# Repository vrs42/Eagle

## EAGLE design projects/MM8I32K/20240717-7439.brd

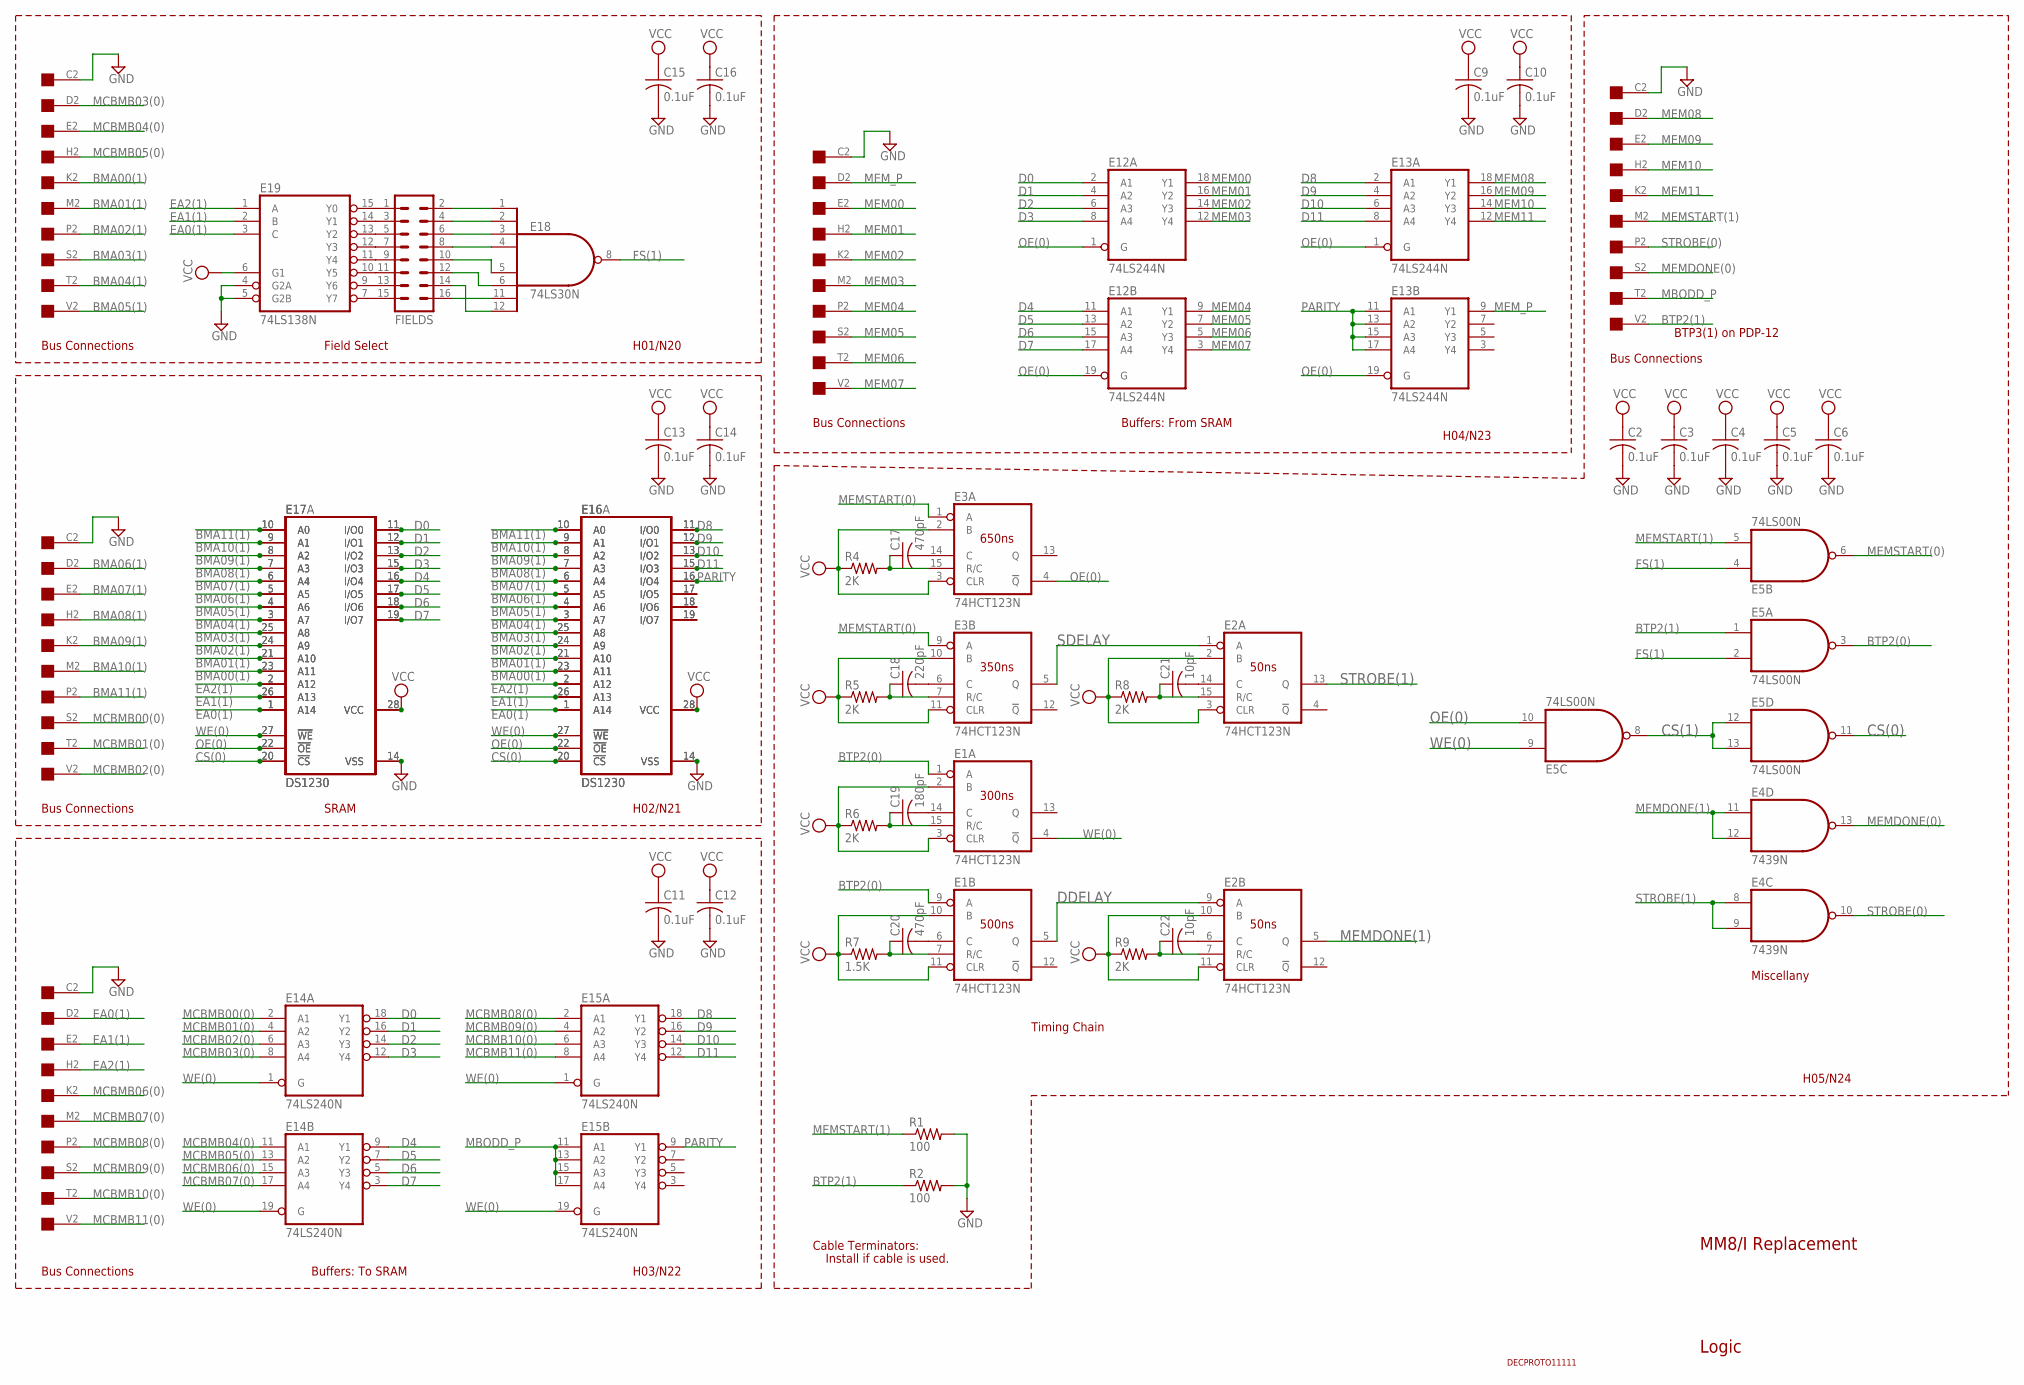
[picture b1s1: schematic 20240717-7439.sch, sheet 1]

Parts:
C2, C3, C4, C5, C6, C9, C10, C11, C12, C13, C14, C15, C16: 0.1uF; C050-025X075
C17, C20: 470pF; C050-025X075
C18: 220pF; C050-025X075
C19: 180pF; C050-025X075
C21, C22: 10pF; C050-025X075
E1, E2, E3: 74HCT123N; DIL16
E4: 7439N; DIL14
E5: 74LS00N; DIL14
E12, E13: 74LS244N; DIL20
E14, E15: 74LS240N; DIL20
E16, E17: DS1230; DIL28-6
E16A, E17A: DS1230; DIL28-3
E18: 74LS30N; DIL14
E19: 74LS138N; DIL16
FIELDS: MA08-2
H01, H02, H03, H04, H05: EDGE-CON1
R1, R2: 100; 0207/10
R4, R5, R6, R8, R9: 2K; 0207/10
R7: 1.5K; 0207/10
U$6: DECPROTO11111

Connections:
BMA00(1): E16.23 (A11), E16A.23 (A11), E17.23 (A11), E17A.23 (A11), H01.K2; also elsewhere on the board
BMA01(1): E16.21 (A10), E16A.21 (A10), E17.21 (A10), E17A.21 (A10), H01.M2; also elsewhere on the board
BMA02(1): E16.24 (A9), E16A.24 (A9), E17.24 (A9), E17A.24 (A9), H01.P2; also elsewhere on the board
BMA03(1): E16.25 (A8), E16A.25 (A8), E17.25 (A8), E17A.25 (A8), H01.S2; also elsewhere on the board
BMA04(1): E16.3 (A7), E16A.3 (A7), E17.3 (A7), E17A.3 (A7), H01.T2; also elsewhere on the board
BMA05(1): E16.4 (A6), E16A.4 (A6), E17.4 (A6), E17A.4 (A6), H01.V2; also elsewhere on the board
BMA06(1): E16.5 (A5), E16A.5 (A5), E17.5 (A5), E17A.5 (A5), H02.D2; also elsewhere on the board
BMA07(1): E16.6 (A4), E16A.6 (A4), E17.6 (A4), E17A.6 (A4), H02.E2; also elsewhere on the board
BMA08(1): E16.7 (A3), E16A.7 (A3), E17.7 (A3), E17A.7 (A3), H02.H2; also elsewhere on the board
BMA09(1): E16.8 (A2), E16A.8 (A2), E17.8 (A2), E17A.8 (A2), H02.K2; also elsewhere on the board
BMA10(1): E16.9 (A1), E16A.9 (A1), E17.9 (A1), E17A.9 (A1), H02.M2; also elsewhere on the board
BMA11(1): E16.10 (A0), E16A.10 (A0), E17.10 (A0), E17A.10 (A0), H02.P2; also elsewhere on the board
BTP2(0): E1.1 (A), E1.9 (A), E5.3 (O)
BTP2(1): E5.1 (I0), H05.V2, R2.1
CS(0): E5.11 (O), E16.20 (!CS), E16A.20 (!CS), E17.20 (!CS), E17A.20 (!CS); also elsewhere on the board
CS(1): E5.8 (O), E5.12 (I0), E5.13 (I1)
D0: E12.2 (A1), E14.18 (Y1), E17.11 (I/O0), E17A.11 (I/O0); also elsewhere on the board
D1: E12.4 (A2), E14.16 (Y2), E17.12 (I/O1), E17A.12 (I/O1); also elsewhere on the board
D2: E12.6 (A3), E14.14 (Y3), E17.13 (I/O2), E17A.13 (I/O2); also elsewhere on the board
D3: E12.8 (A4), E14.12 (Y4), E17.15 (I/O3), E17A.15 (I/O3); also elsewhere on the board
D4: E12.11 (A1), E14.9 (Y1), E17.16 (I/O4), E17A.16 (I/O4); also elsewhere on the board
D5: E12.13 (A2), E14.7 (Y2), E17.17 (I/O5), E17A.17 (I/O5); also elsewhere on the board
D6: E12.15 (A3), E14.5 (Y3), E17.18 (I/O6), E17A.18 (I/O6); also elsewhere on the board
D7: E12.17 (A4), E14.3 (Y4), E17.19 (I/O7), E17A.19 (I/O7); also elsewhere on the board
D8: E13.2 (A1), E15.18 (Y1), E16.11 (I/O0), E16A.11 (I/O0); also elsewhere on the board
D9: E13.4 (A2), E15.16 (Y2), E16.12 (I/O1), E16A.12 (I/O1); also elsewhere on the board
D10: E13.6 (A3), E15.14 (Y3), E16.13 (I/O2), E16A.13 (I/O2); also elsewhere on the board
D11: E13.8 (A4), E15.12 (Y4), E16.15 (I/O3), E16A.15 (I/O3); also elsewhere on the board
DDELAY: E1.5 (Q), E2.9 (A)
EA0(1): E16.1 (A14), E16A.1 (A14), E17.1 (A14), E17A.1 (A14), E19.3 (C), H03.D2; also elsewhere on the board
EA1(1): E16.26 (A13), E16A.26 (A13), E17.26 (A13), E17A.26 (A13), E19.2 (B), H03.E2; also elsewhere on the board
EA2(1): E16.2 (A12), E16A.2 (A12), E17.2 (A12), E17A.2 (A12), E19.1 (A), H03.H2; also elsewhere on the board
FS(1): E5.2 (I1), E5.4 (I0), E18.8 (O); also elsewhere on the board
GND: C2.2, C3.2, C4.2, C5.2, C6.2, C9.2, C10.2, C11.2, C12.2, C13.2, C14.2, C15.2, C16.2, E1.8 (GND), E2.8 (GND), E3.8 (GND), E4.7 (GND), E5.7 (GND), E12.10 (GND), E13.10 (GND), E14.10 (GND), E15.10 (GND), E16.14 (VSS), E16A.14 (VSS), E17.14 (VSS), E17A.14 (VSS), E18.7 (GND), E19.4 (G2A), E19.5 (G2B), E19.8 (GND), H01.C2, H02.C2, H03.C2, H04.C2, H05.C2, R1.2, R2.2; also elsewhere on the board
MBODD_P: E15.11 (A1), E15.13 (A2), E15.15 (A3), E15.17 (A4), H05.T2; also elsewhere on the board
MCBMB00(0): E14.2 (A1), H02.S2; also elsewhere on the board
MCBMB01(0): E14.4 (A2), H02.T2; also elsewhere on the board
MCBMB02(0): E14.6 (A3), H02.V2; also elsewhere on the board
MCBMB03(0): E14.8 (A4), H01.D2; also elsewhere on the board
MCBMB04(0): E14.11 (A1), H01.E2; also elsewhere on the board
MCBMB05(0): E14.13 (A2), H01.H2; also elsewhere on the board
MCBMB06(0): E14.15 (A3), H03.K2
MCBMB07(0): E14.17 (A4), H03.M2
MCBMB08(0): E15.2 (A1), H03.P2
MCBMB09(0): E15.4 (A2), H03.S2
MCBMB10(0): E15.6 (A3), H03.T2
MCBMB11(0): E15.8 (A4), H03.V2
MEM00: E12.18 (Y1), H04.E2
MEM01: E12.16 (Y2), H04.H2
MEM02: E12.14 (Y3), H04.K2
MEM03: E12.12 (Y4), H04.M2
MEM04: E12.9 (Y1), H04.P2
MEM05: E12.7 (Y2), H04.S2
MEM06: E12.5 (Y3), H04.T2
MEM07: E12.3 (Y4), H04.V2
MEM08: E13.18 (Y1), H05.D2; also elsewhere on the board
MEM09: E13.16 (Y2), H05.E2; also elsewhere on the board
MEM10: E13.14 (Y3), H05.H2; also elsewhere on the board
MEM11: E13.12 (Y4), H05.K2; also elsewhere on the board
MEMDONE(0): E4.13 (O), H05.S2
MEMDONE(1): E2.5 (Q), E4.11 (I0), E4.12 (I1)
MEMSTART(0): E3.1 (A), E3.9 (A), E5.6 (O)
MEMSTART(1): E5.5 (I1), H05.M2, R1.1
MEM_P: E13.9 (Y1), H04.D2
unnamed: E16.17 (I/O5), E16A.17 (I/O5)
unnamed: E16.18 (I/O6), E16A.18 (I/O6)
unnamed: E16.19 (I/O7), E16A.19 (I/O7)
unnamed: C17.1, E3.15 (R/C), R4.2
unnamed: C17.2, E3.14 (C)
unnamed: C18.1, E3.7 (R/C), R5.2
unnamed: C18.2, E3.6 (C)
unnamed: C19.1, E1.15 (R/C), R6.2
unnamed: C19.2, E1.14 (C)
unnamed: C20.1, E1.7 (R/C), R7.2
unnamed: C20.2, E1.6 (C)
unnamed: C21.1, E2.15 (R/C), R8.2
unnamed: C21.2, E2.14 (C)
unnamed: C22.1, E2.7 (R/C), R9.2
unnamed: C22.2, E2.6 (C)
unnamed: E19.15 (Y0), FIELDS.1
unnamed: E19.14 (Y1), FIELDS.3
unnamed: E19.13 (Y2), FIELDS.5
unnamed: E19.12 (Y3), FIELDS.7
unnamed: E19.11 (Y4), FIELDS.9
unnamed: E19.10 (Y5), FIELDS.11
unnamed: E19.9 (Y6), FIELDS.13
unnamed: E19.7 (Y7), FIELDS.15
unnamed: E18.4 (I3), FIELDS.8
unnamed: E18.3 (I2), FIELDS.6
unnamed: E18.2 (I1), FIELDS.4
unnamed: E18.1 (I0), FIELDS.2
unnamed: E18.5 (I4), FIELDS.10
unnamed: E18.6 (I5), FIELDS.12
unnamed: E18.12 (I7), FIELDS.14
unnamed: E18.11 (I6), FIELDS.16
OE(0): E3.4 (!Q), E5.10 (I1), E12.1 (G), E12.19 (G), E13.1 (G), E13.19 (G), E16.22 (!OE), E16A.22 (!OE), E17.22 (!OE), E17A.22 (!OE); also elsewhere on the board
PARITY: E13.11 (A1), E13.13 (A2), E13.15 (A3), E13.17 (A4), E15.9 (Y1), E16.16 (I/O4), E16A.16 (I/O4); also elsewhere on the board
SDELAY: E2.1 (A), E3.5 (Q)
STROBE(0): E4.10 (O), H05.P2
STROBE(1): E2.13 (Q), E4.8 (I0), E4.9 (I1)
VCC: C2.1, C3.1, C4.1, C5.1, C6.1, C9.1, C10.1, C11.1, C12.1, C13.1, C14.1, C15.1, C16.1, E1.2 (B), E1.3 (CLR), E1.10 (B), E1.11 (CLR), E1.16 (VCC), E2.2 (B), E2.3 (CLR), E2.10 (B), E2.11 (CLR), E2.16 (VCC), E3.2 (B), E3.3 (CLR), E3.10 (B), E3.11 (CLR), E3.16 (VCC), E4.14 (VCC), E5.14 (VCC), E12.20 (VCC), E13.20 (VCC), E14.20 (VCC), E15.20 (VCC), E16.28 (VCC), E16A.28 (VCC), E17.28 (VCC), E17A.28 (VCC), E18.14 (VCC), E19.6 (G1), E19.16 (VCC), R4.1, R5.1, R6.1, R7.1, R8.1, R9.1; also elsewhere on the board
WE(0): E1.4 (!Q), E5.9 (I0), E14.1 (G), E14.19 (G), E15.1 (G), E15.19 (G), E16.27 (!WE), E16A.27 (!WE), E17.27 (!WE), E17A.27 (!WE); also elsewhere on the board

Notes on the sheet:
H01/N20
H02/N21
H03/N22
H04/N23
Field Select
SRAM
MM8/I Replacement
Buffers: To SRAM
Buffers: From SRAM
Timing Chain
BTP3(1) on PDP-12
Miscellany
H05/N24
Logic
Bus Connections
Cable Terminators:
Install if cable is used.
650ns
350ns
50ns
300ns
500ns

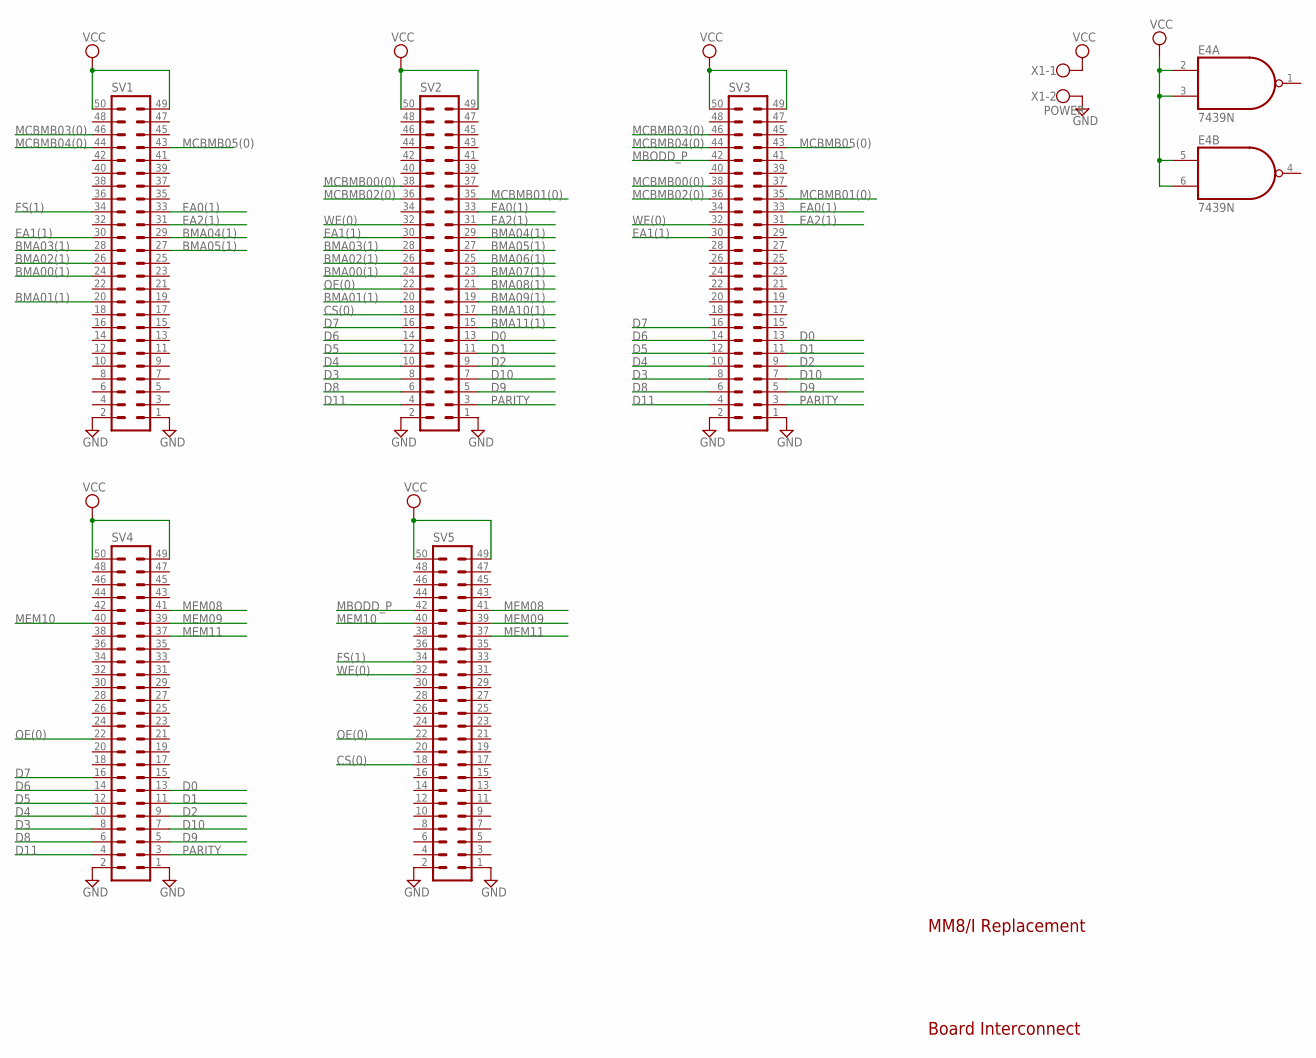
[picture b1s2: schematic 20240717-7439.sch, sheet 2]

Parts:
E4: 7439N; DIL14
SV1, SV2, SV3, SV4, SV5: ML50L
X1: POWER; W237-102

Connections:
BMA00(1): SV1.24, SV2.24; also elsewhere on the board
BMA01(1): SV1.20, SV2.20; also elsewhere on the board
BMA02(1): SV1.26, SV2.26; also elsewhere on the board
BMA03(1): SV1.28, SV2.28; also elsewhere on the board
BMA04(1): SV1.29, SV2.29; also elsewhere on the board
BMA05(1): SV1.27, SV2.27; also elsewhere on the board
BMA06(1): SV2.25; also elsewhere on the board
BMA07(1): SV2.23; also elsewhere on the board
BMA08(1): SV2.21; also elsewhere on the board
BMA09(1): SV2.19; also elsewhere on the board
BMA10(1): SV2.17; also elsewhere on the board
BMA11(1): SV2.15; also elsewhere on the board
CS(0): SV2.18, SV5.18; also elsewhere on the board
D0: SV2.13, SV3.13, SV4.13; also elsewhere on the board
D1: SV2.11, SV3.11, SV4.11; also elsewhere on the board
D2: SV2.9, SV3.9, SV4.9; also elsewhere on the board
D3: SV2.8, SV3.8, SV4.8; also elsewhere on the board
D4: SV2.10, SV3.10, SV4.10; also elsewhere on the board
D5: SV2.12, SV3.12, SV4.12; also elsewhere on the board
D6: SV2.14, SV3.14, SV4.14; also elsewhere on the board
D7: SV2.16, SV3.16, SV4.16; also elsewhere on the board
D8: SV2.6, SV3.6, SV4.6; also elsewhere on the board
D9: SV2.5, SV3.5, SV4.5; also elsewhere on the board
D10: SV2.7, SV3.7, SV4.7; also elsewhere on the board
D11: SV2.4, SV3.4, SV4.4; also elsewhere on the board
EA0(1): SV1.33, SV2.33, SV3.33; also elsewhere on the board
EA1(1): SV1.30, SV2.30, SV3.30; also elsewhere on the board
EA2(1): SV1.31, SV2.31, SV3.31; also elsewhere on the board
FS(1): SV1.34, SV5.34; also elsewhere on the board
GND: E4.7 (GND), SV1.1, SV1.2, SV2.1, SV2.2, SV3.1, SV3.2, SV4.1, SV4.2, SV5.1, SV5.2, X1.2; also elsewhere on the board
MBODD_P: SV3.42, SV5.42; also elsewhere on the board
MCBMB00(0): SV2.38, SV3.38; also elsewhere on the board
MCBMB01(0): SV2.35, SV3.35; also elsewhere on the board
MCBMB02(0): SV2.36, SV3.36; also elsewhere on the board
MCBMB03(0): SV1.46, SV3.46; also elsewhere on the board
MCBMB04(0): SV1.44, SV3.44; also elsewhere on the board
MCBMB05(0): SV1.43, SV3.43; also elsewhere on the board
MEM08: SV4.41, SV5.41; also elsewhere on the board
MEM09: SV4.39, SV5.39; also elsewhere on the board
MEM10: SV4.40, SV5.40; also elsewhere on the board
MEM11: SV4.37, SV5.37; also elsewhere on the board
OE(0): SV2.22, SV4.22, SV5.22; also elsewhere on the board
PARITY: SV2.3, SV3.3, SV4.3; also elsewhere on the board
VCC: E4.2 (I0), E4.3 (I1), E4.5 (I0), E4.6 (I1), E4.14 (VCC), SV1.49, SV1.50, SV2.49, SV2.50, SV3.49, SV3.50, SV4.49, SV4.50, SV5.49, SV5.50, X1.1; also elsewhere on the board
WE(0): SV2.32, SV3.32, SV5.32; also elsewhere on the board

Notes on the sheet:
Board Interconnect
MM8/I Replacement

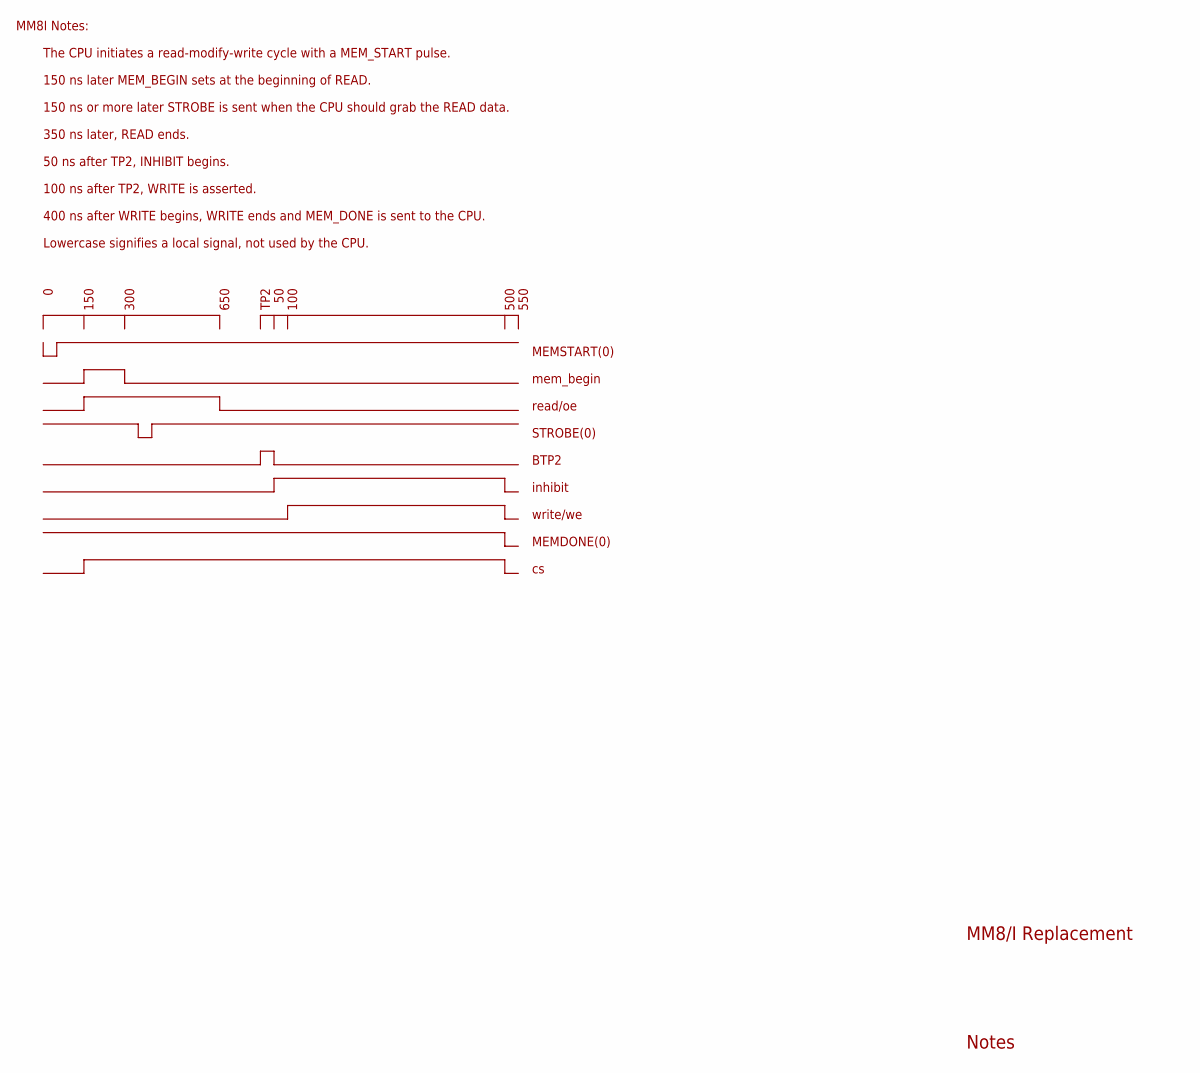
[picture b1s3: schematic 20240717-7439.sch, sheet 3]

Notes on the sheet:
Notes
The CPU initiates a read-modify-write cycle with a MEM_START pulse.
150 ns later MEM_BEGIN sets at the beginning of READ.
150 ns or more later STROBE is sent when the CPU should grab the READ data.
50 ns after TP2, INHIBIT begins.
100 ns after TP2, WRITE is asserted.
400 ns after WRITE begins, WRITE ends and MEM_DONE is sent to the CPU.
350 ns later, READ ends.
150
300
650
TP2
100
500
MEMSTART(0)
mem_begin
read/oe
STROBE(0)
BTP2
inhibit
write/we
MEMDONE(0)
Lowercase signifies a local signal, not used by the CPU.
550
MM8I Notes:
MM8/I Replacement

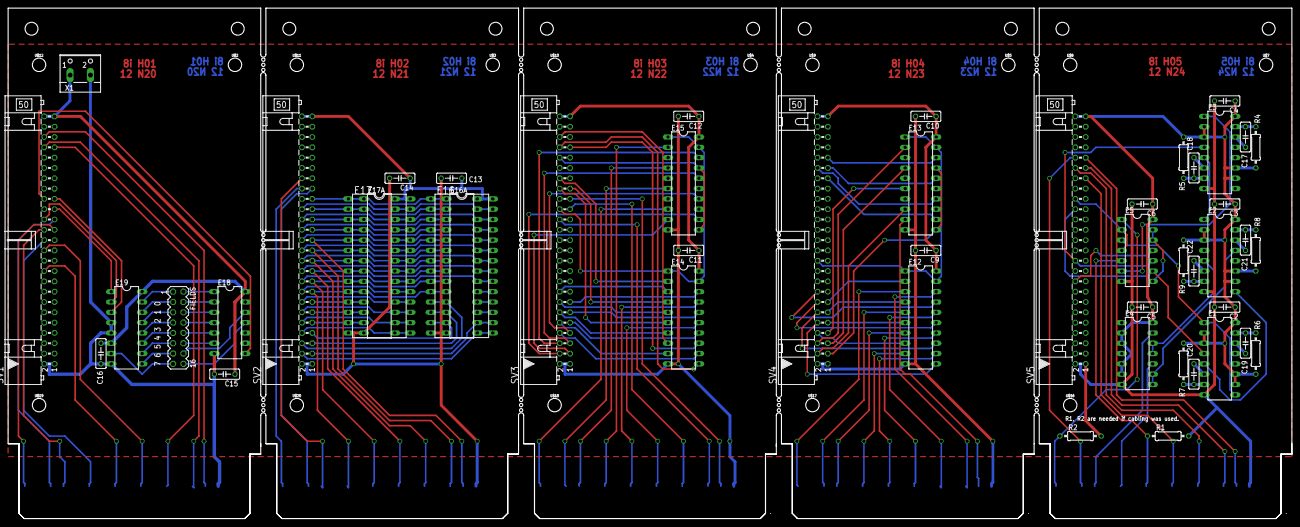
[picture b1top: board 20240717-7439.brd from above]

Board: 2 copper layers, 316.2 x 125.7 mm, 70 parts (0 on the bottom side), 102 nets.

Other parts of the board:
U$2, U$3, U$4, U$5, U$7, U$8, U$9, U$10, U$11, U$12, U$16, U$17, U$18, U$19, U$20: STAND-OFF

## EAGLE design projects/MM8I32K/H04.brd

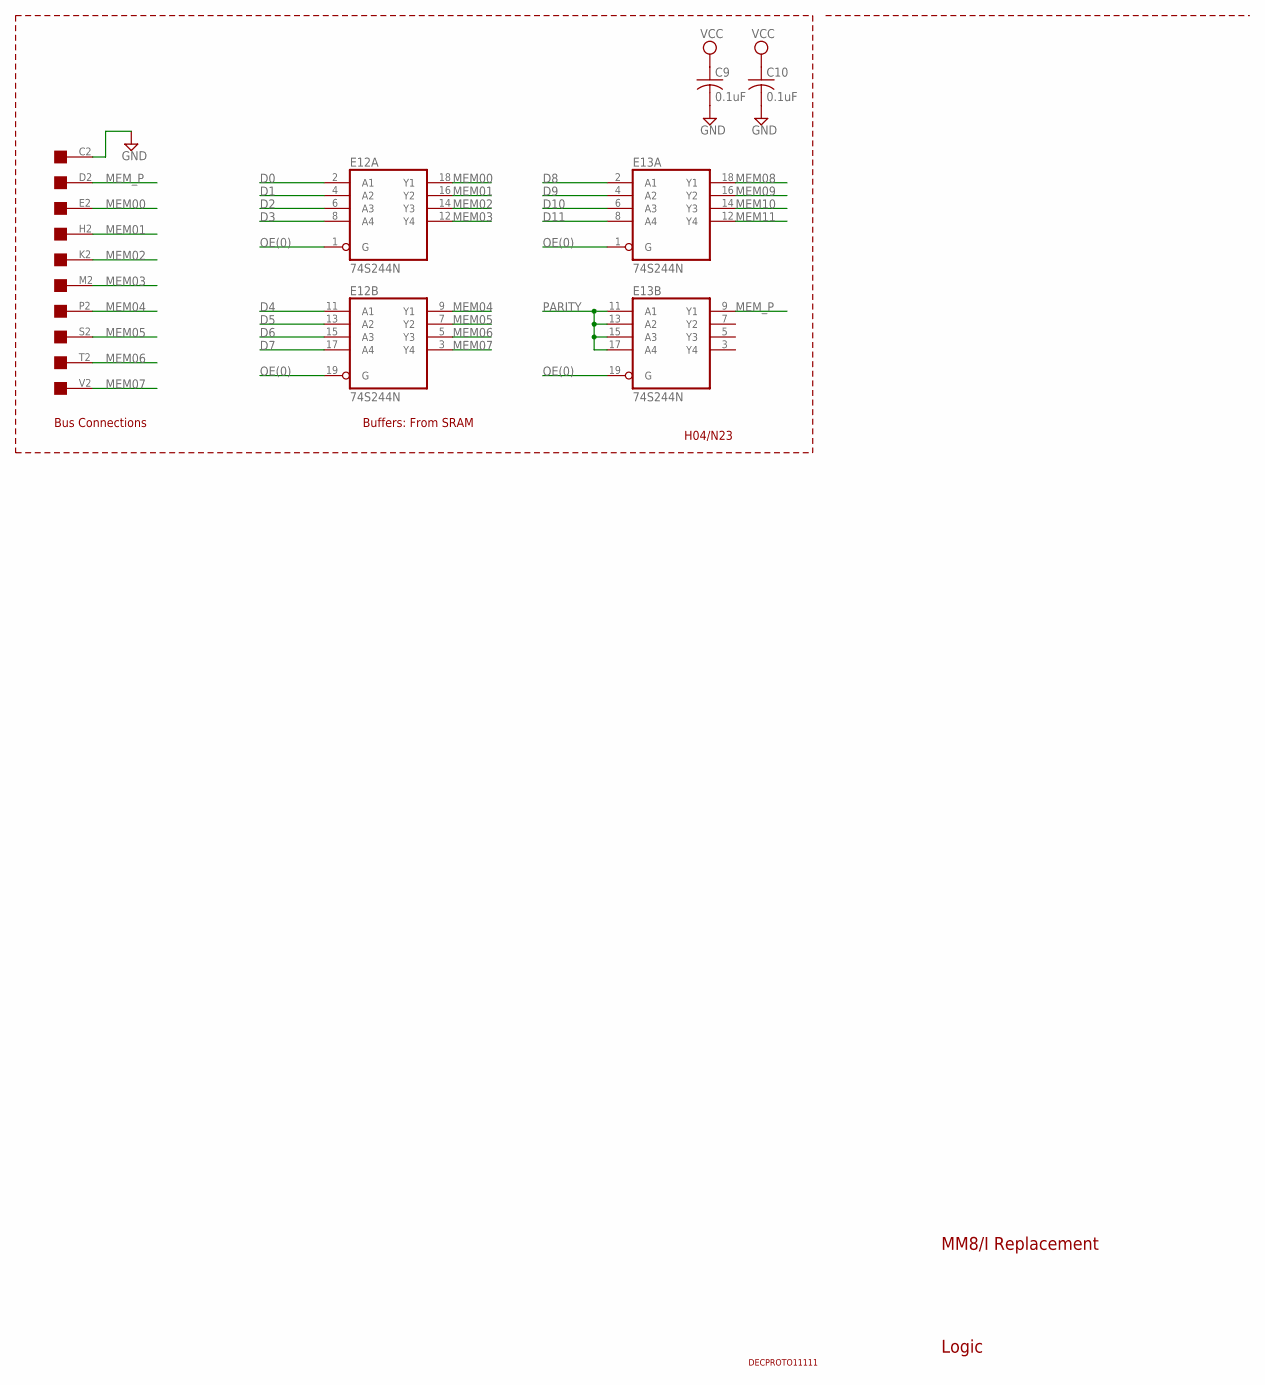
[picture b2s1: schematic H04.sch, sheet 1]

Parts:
C9, C10: 0.1uF; C050-025X075
E12, E13: 74S244N; DIL20
H04: EDGE-CON1
U$6: DECPROTO11111

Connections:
D0: E12.2 (A1); also elsewhere on the board
D1: E12.4 (A2); also elsewhere on the board
D2: E12.6 (A3); also elsewhere on the board
D3: E12.8 (A4); also elsewhere on the board
D4: E12.11 (A1); also elsewhere on the board
D5: E12.13 (A2); also elsewhere on the board
D6: E12.15 (A3); also elsewhere on the board
D7: E12.17 (A4); also elsewhere on the board
D8: E13.2 (A1); also elsewhere on the board
D9: E13.4 (A2); also elsewhere on the board
D10: E13.6 (A3); also elsewhere on the board
D11: E13.8 (A4); also elsewhere on the board
GND: C9.2, C10.2, E12.10 (GND), E13.10 (GND), H04.C2; also elsewhere on the board
MEM00: E12.18 (Y1), H04.E2
MEM01: E12.16 (Y2), H04.H2
MEM02: E12.14 (Y3), H04.K2
MEM03: E12.12 (Y4), H04.M2
MEM04: E12.9 (Y1), H04.P2
MEM05: E12.7 (Y2), H04.S2
MEM06: E12.5 (Y3), H04.T2
MEM07: E12.3 (Y4), H04.V2
MEM08: E13.18 (Y1); also elsewhere on the board
MEM09: E13.16 (Y2); also elsewhere on the board
MEM10: E13.14 (Y3); also elsewhere on the board
MEM11: E13.12 (Y4); also elsewhere on the board
MEM_P: E13.9 (Y1), H04.D2
OE(0): E12.1 (G), E12.19 (G), E13.1 (G), E13.19 (G); also elsewhere on the board
PARITY: E13.11 (A1), E13.13 (A2), E13.15 (A3), E13.17 (A4); also elsewhere on the board
VCC: C9.1, C10.1, E12.20 (VCC), E13.20 (VCC); also elsewhere on the board

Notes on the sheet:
H04/N23
MM8/I Replacement
Buffers: From SRAM
Logic
Bus Connections

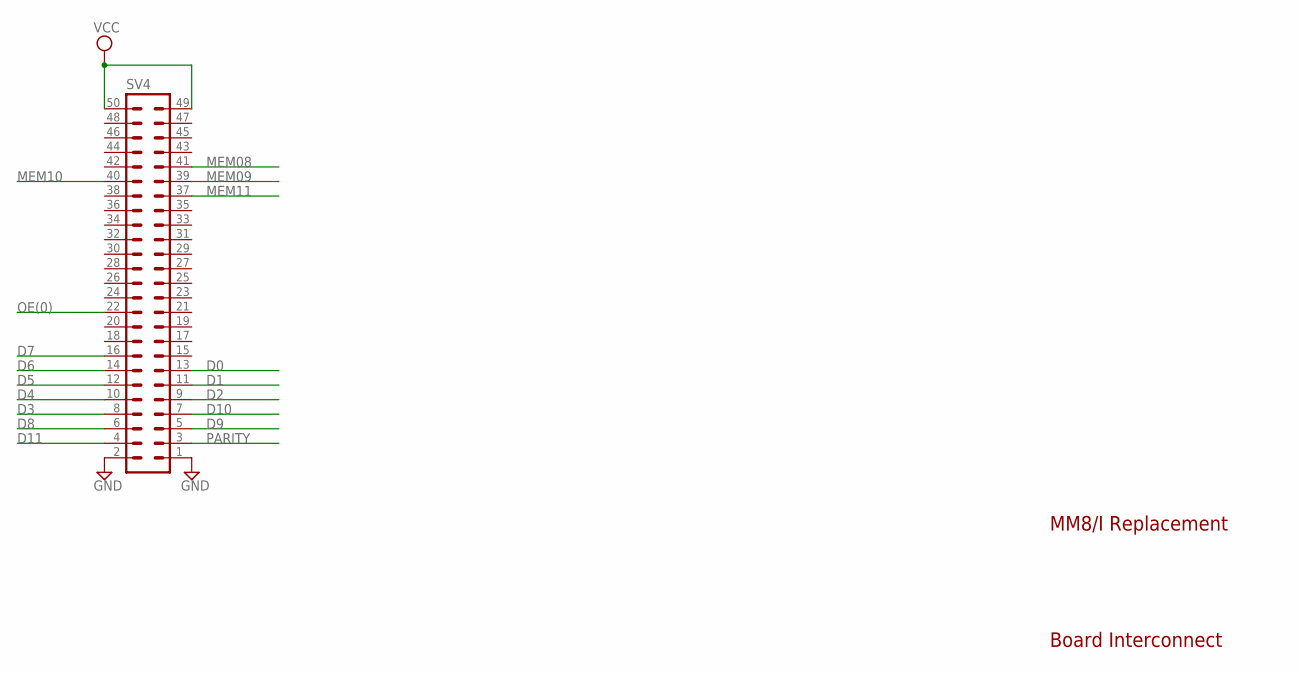
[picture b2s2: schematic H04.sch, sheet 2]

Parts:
SV4: ML50L

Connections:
D0: SV4.13; also elsewhere on the board
D1: SV4.11; also elsewhere on the board
D2: SV4.9; also elsewhere on the board
D3: SV4.8; also elsewhere on the board
D4: SV4.10; also elsewhere on the board
D5: SV4.12; also elsewhere on the board
D6: SV4.14; also elsewhere on the board
D7: SV4.16; also elsewhere on the board
D8: SV4.6; also elsewhere on the board
D9: SV4.5; also elsewhere on the board
D10: SV4.7; also elsewhere on the board
D11: SV4.4; also elsewhere on the board
GND: SV4.1, SV4.2; also elsewhere on the board
MEM08: SV4.41; also elsewhere on the board
MEM09: SV4.39; also elsewhere on the board
MEM10: SV4.40; also elsewhere on the board
MEM11: SV4.37; also elsewhere on the board
OE(0): SV4.22; also elsewhere on the board
PARITY: SV4.3; also elsewhere on the board
VCC: SV4.49, SV4.50; also elsewhere on the board

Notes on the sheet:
Board Interconnect
MM8/I Replacement

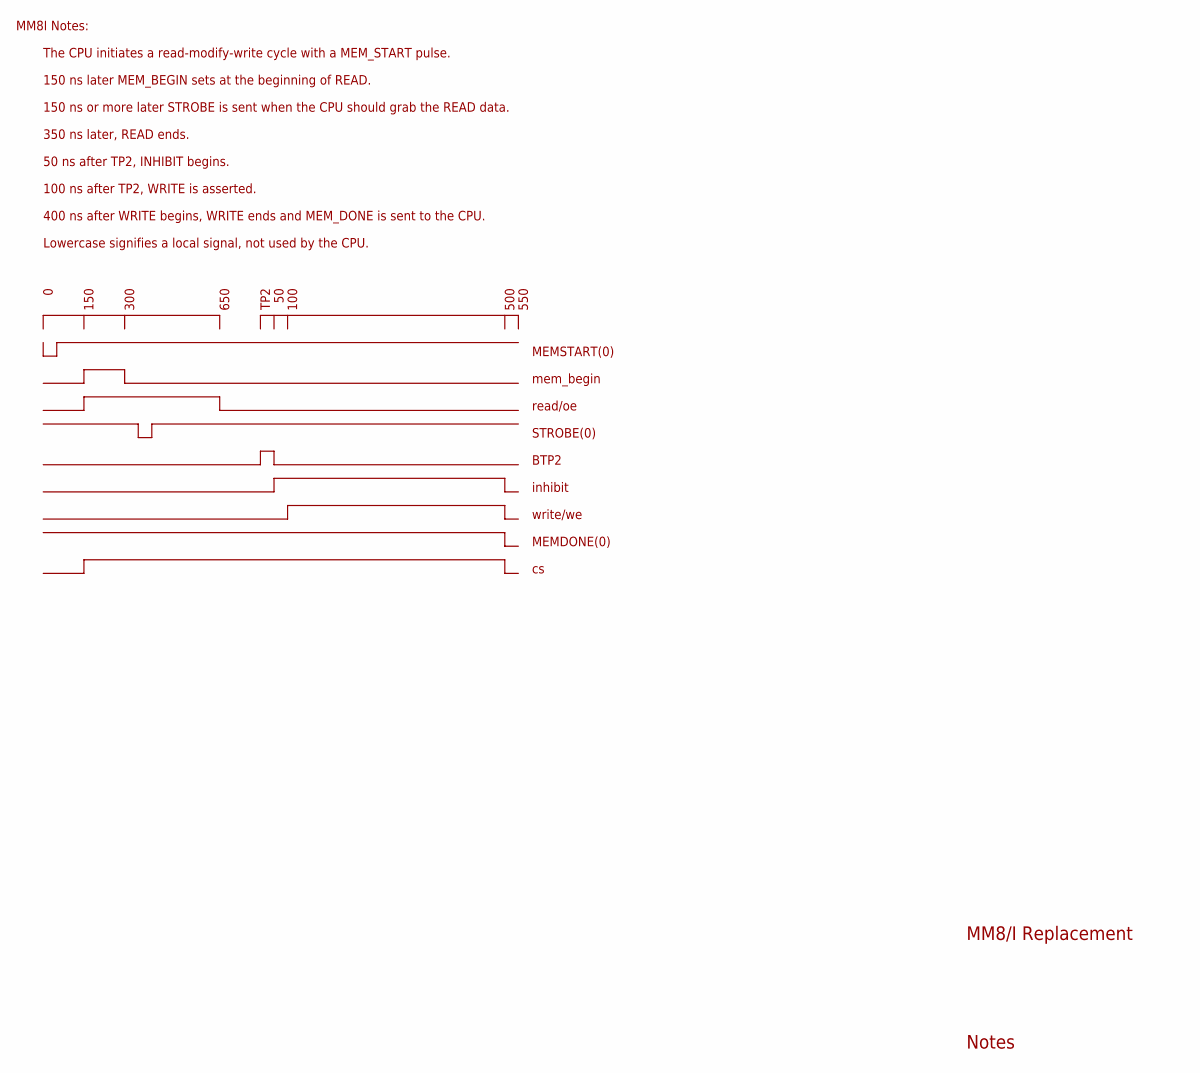
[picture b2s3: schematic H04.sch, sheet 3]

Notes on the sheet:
Notes
The CPU initiates a read-modify-write cycle with a MEM_START pulse.
150 ns later MEM_BEGIN sets at the beginning of READ.
150 ns or more later STROBE is sent when the CPU should grab the READ data.
50 ns after TP2, INHIBIT begins.
100 ns after TP2, WRITE is asserted.
400 ns after WRITE begins, WRITE ends and MEM_DONE is sent to the CPU.
350 ns later, READ ends.
150
300
650
TP2
100
500
MEMSTART(0)
mem_begin
read/oe
STROBE(0)
BTP2
inhibit
write/we
MEMDONE(0)
Lowercase signifies a local signal, not used by the CPU.
550
MM8I Notes:
MM8/I Replacement

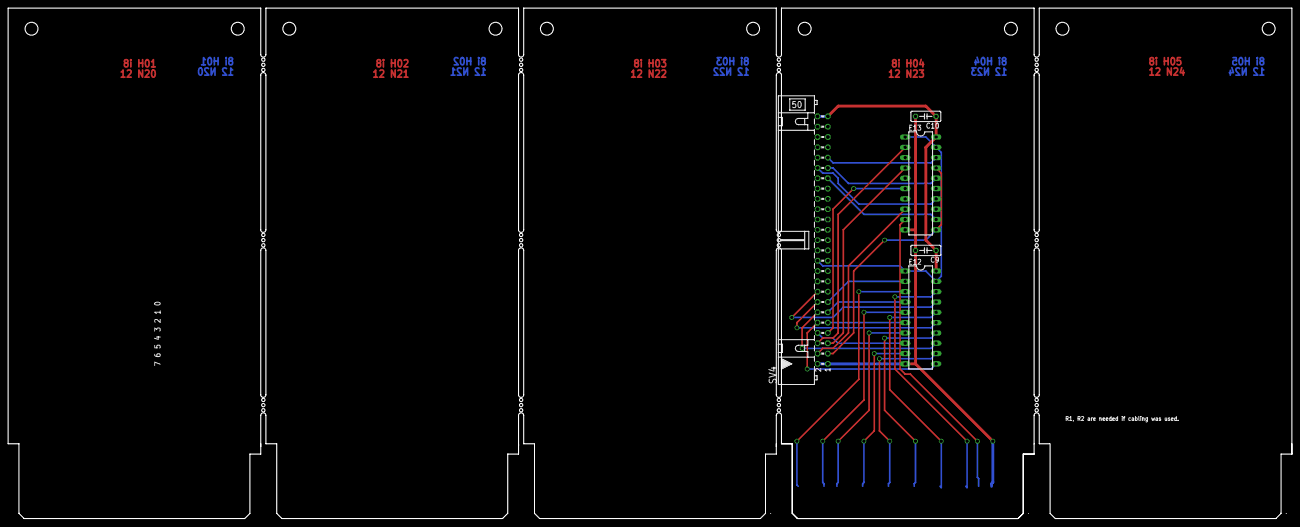
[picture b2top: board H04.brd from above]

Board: 2 copper layers, 316.2 x 125.7 mm, 7 parts (0 on the bottom side), 29 nets.

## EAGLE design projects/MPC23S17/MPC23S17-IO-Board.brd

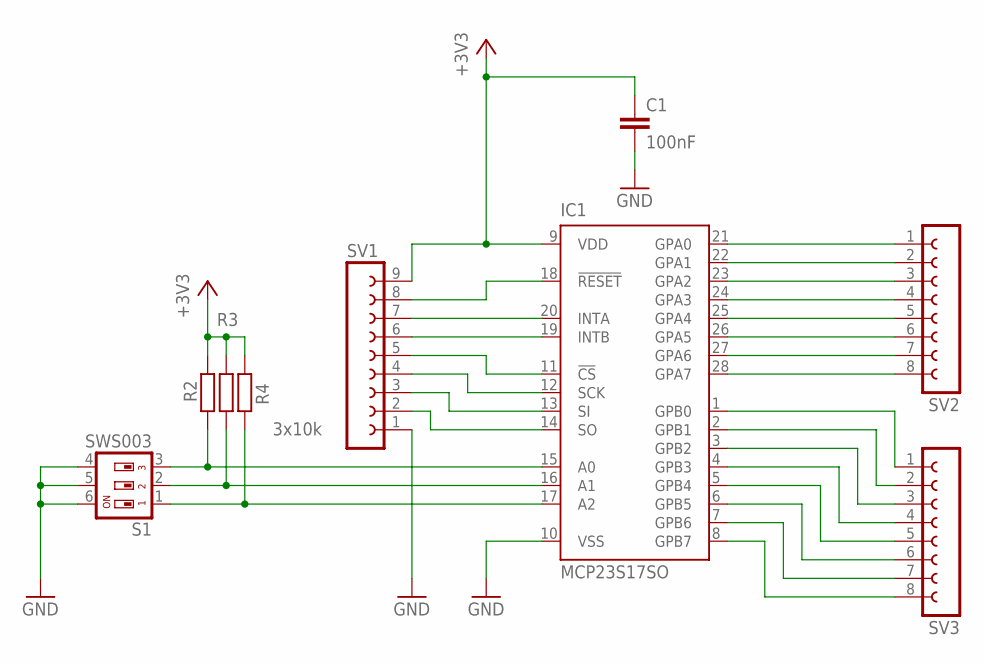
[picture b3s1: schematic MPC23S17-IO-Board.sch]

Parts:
C1: 100nF; C1206
IC1: MCP23S17SO; SO28W
R2, R3: 10k; M1206
R4: 3x10k; M1206
S1: SWS003; SMS-003
SV1: FE09-1; FE09
SV2, SV3: FE08-1; FE08

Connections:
+3V3: C1.1, IC1.9 (VDD), R2.1, R3.1, R4.1, SV1.9
GND: C1.2, IC1.10 (VSS), S1.4, S1.5, S1.6, SV1.1
unnamed: IC1.21 (GPA0), SV2.1
unnamed: IC1.22 (GPA1), SV2.2
unnamed: IC1.23 (GPA2), SV2.3
unnamed: IC1.24 (GPA3), SV2.4
unnamed: IC1.25 (GPA4), SV2.5
unnamed: IC1.26 (GPA5), SV2.6
unnamed: IC1.27 (GPA6), SV2.7
unnamed: IC1.28 (GPA7), SV2.8
unnamed: IC1.1 (GPB0), SV3.1
unnamed: IC1.2 (GPB1), SV3.2
unnamed: IC1.3 (GPB2), SV3.3
unnamed: IC1.4 (GPB3), SV3.4
unnamed: IC1.5 (GPB4), SV3.5
unnamed: IC1.15 (A0), R2.2, S1.3
unnamed: IC1.16 (A1), R3.2, S1.2
unnamed: IC1.17 (A2), R4.2, S1.1
unnamed: IC1.6 (GPB5), SV3.6
unnamed: IC1.7 (GPB6), SV3.7
unnamed: IC1.19 (INTB), SV1.6
unnamed: IC1.14 (SO), SV1.2
unnamed: IC1.13 (SI), SV1.3
unnamed: IC1.12 (SCK), SV1.4
unnamed: IC1.11 (!CS), SV1.5
unnamed: IC1.20 (INTA), SV1.7
unnamed: IC1.18 (!RESET), SV1.8
unnamed: IC1.8 (GPB7), SV3.8

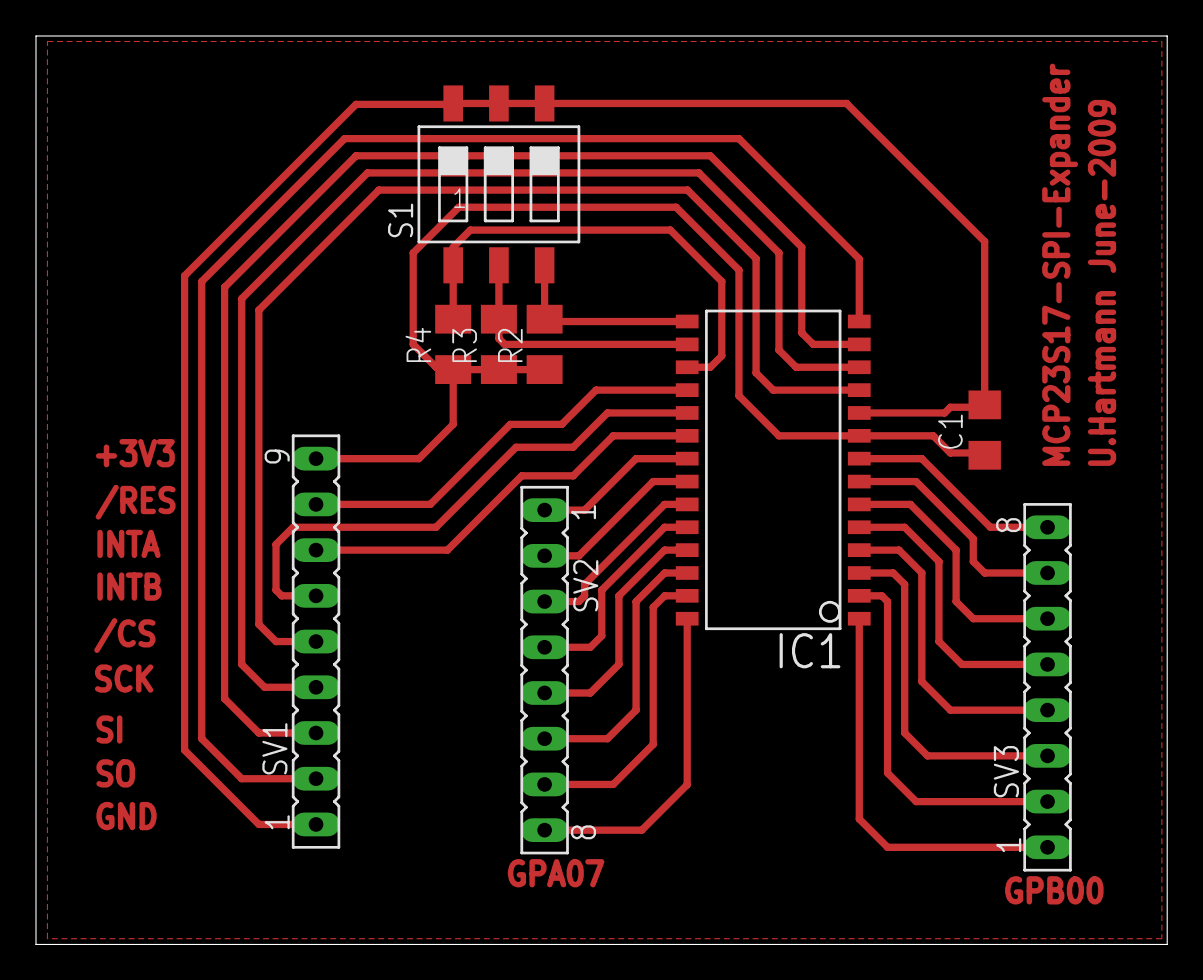
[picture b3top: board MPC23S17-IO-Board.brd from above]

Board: 2 copper layers, 62.8 x 50.5 mm, 9 parts (0 on the bottom side), 28 nets.

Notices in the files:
parts and their libraries:
SparkFun-Hardware: Licensing: Creative Commons ShareAlike 4.0 International - https://creativecommons.org/licenses/by-sa/4.0
